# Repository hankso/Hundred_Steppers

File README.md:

## Hundred Steppers
An arduino library to control hundreds of steppers with as less pins or
arduinos as possible.

[74HC595](https://www.arduino.cc/en/Tutorial/ShiftOut) is needed to extend the
GPIO number of arduino.

To offer enough current for steppers, you may need UNL2803(8 channel NPN
darlington triodes, 500mA@50V max)

If you have used arduino library
[`Stepper`](https://www.arduino.cc/en/Reference/Stepper) and
[`Adafruit_NeoPixel`](https://github.com/adafruit/Adafruit_NeoPixel) before,
you may find this API familiar because I name these functions similar with them.

## How to use
- Download zip file
- Unzip in your arduino libraries directory. It can be `~/arduino/libraries`
or something like `C:\Program Files\Arduino\libraries`.
- open your arduino IDE and try include library `include <Hundred_Steppers.h>`,
also there is an [example](example/control_steppers) available.

## Hardware
- There is an example hardware design available in `Eagle` format.
- 74HC595 pins
    - ST_CP --> latchPin
    - SH_CP --> clockPin
    - DS --> dataPin
    - OE --> enablePin
    - MR --> clearPin

## API

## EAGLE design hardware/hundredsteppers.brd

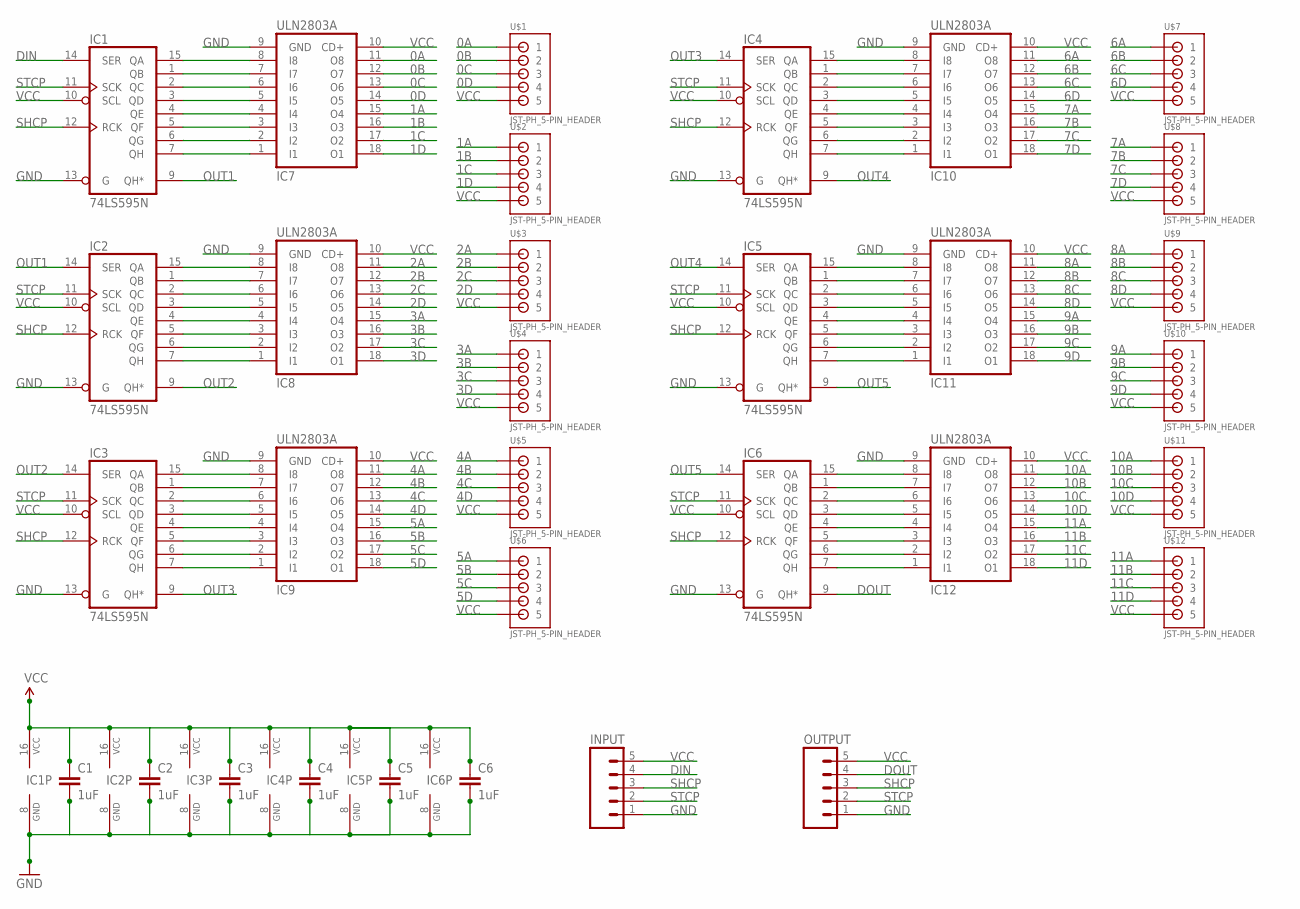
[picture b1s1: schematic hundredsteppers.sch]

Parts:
C1, C2, C3, C4, C5, C6: 1uF; 0805
IC1, IC2, IC3, IC4, IC5, IC6: 74LS595N; DIL16
IC7, IC8, IC9, IC10, IC11, IC12: ULN2803A; DIL18
INPUT: M05PTH; 1X05
OUTPUT: M05PTH; 1X05
U$1, U$2, U$3, U$4, U$5, U$6, U$7, U$8, U$9, U$10, U$11, U$12: JST-PH_5-PIN_HEADER; JST_B5B-PH_HEADER

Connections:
0A: IC7.11 (O8), U$1.P1 (1)
0B: IC7.12 (O7), U$1.P2 (2)
0C: IC7.13 (O6), U$1.P3 (3)
0D: IC7.14 (O5), U$1.P4 (4)
1A: IC7.15 (O4), U$2.P1 (1)
1B: IC7.16 (O3), U$2.P2 (2)
1C: IC7.17 (O2), U$2.P3 (3)
1D: IC7.18 (O1), U$2.P4 (4)
2A: IC8.11 (O8), U$3.P1 (1)
2B: IC8.12 (O7), U$3.P2 (2)
2C: IC8.13 (O6), U$3.P3 (3)
2D: IC8.14 (O5), U$3.P4 (4)
3A: IC8.15 (O4), U$4.P1 (1)
3B: IC8.16 (O3), U$4.P2 (2)
3C: IC8.17 (O2), U$4.P3 (3)
3D: IC8.18 (O1), U$4.P4 (4)
4A: IC9.11 (O8), U$5.P1 (1)
4B: IC9.12 (O7), U$5.P2 (2)
4C: IC9.13 (O6), U$5.P3 (3)
4D: IC9.14 (O5), U$5.P4 (4)
5A: IC9.15 (O4), U$6.P1 (1)
5B: IC9.16 (O3), U$6.P2 (2)
5C: IC9.17 (O2), U$6.P3 (3)
5D: IC9.18 (O1), U$6.P4 (4)
6A: IC10.11 (O8), U$7.P1 (1)
6B: IC10.12 (O7), U$7.P2 (2)
6C: IC10.13 (O6), U$7.P3 (3)
6D: IC10.14 (O5), U$7.P4 (4)
7A: IC10.15 (O4), U$8.P1 (1)
7B: IC10.16 (O3), U$8.P2 (2)
7C: IC10.17 (O2), U$8.P3 (3)
7D: IC10.18 (O1), U$8.P4 (4)
8A: IC11.11 (O8), U$9.P1 (1)
8B: IC11.12 (O7), U$9.P2 (2)
8C: IC11.13 (O6), U$9.P3 (3)
8D: IC11.14 (O5), U$9.P4 (4)
9A: IC11.15 (O4), U$10.P1 (1)
9B: IC11.16 (O3), U$10.P2 (2)
9C: IC11.17 (O2), U$10.P3 (3)
9D: IC11.18 (O1), U$10.P4 (4)
10A: IC12.11 (O8), U$11.P1 (1)
10B: IC12.12 (O7), U$11.P2 (2)
10C: IC12.13 (O6), U$11.P3 (3)
10D: IC12.14 (O5), U$11.P4 (4)
11A: IC12.15 (O4), U$12.P1 (1)
11B: IC12.16 (O3), U$12.P2 (2)
11C: IC12.17 (O2), U$12.P3 (3)
11D: IC12.18 (O1), U$12.P4 (4)
DIN: IC1.14 (SER), INPUT.4
DOUT: IC6.9 (QH*), OUTPUT.4
GND: C1.2, C2.2, C3.2, C4.2, C5.2, C6.2, IC1.8 (GND), IC1.13 (G), IC2.8 (GND), IC2.13 (G), IC3.8 (GND), IC3.13 (G), IC4.8 (GND), IC4.13 (G), IC5.8 (GND), IC5.13 (G), IC6.8 (GND), IC6.13 (G), IC7.9 (GND), IC8.9 (GND), IC9.9 (GND), IC10.9 (GND), IC11.9 (GND), IC12.9 (GND), INPUT.1, OUTPUT.1
unnamed: IC1.15 (QA), IC7.8 (I8)
unnamed: IC1.1 (QB), IC7.7 (I7)
unnamed: IC1.2 (QC), IC7.6 (I6)
unnamed: IC1.3 (QD), IC7.5 (I5)
unnamed: IC1.4 (QE), IC7.4 (I4)
unnamed: IC1.5 (QF), IC7.3 (I3)
unnamed: IC1.6 (QG), IC7.2 (I2)
unnamed: IC1.7 (QH), IC7.1 (I1)
unnamed: IC2.15 (QA), IC8.8 (I8)
unnamed: IC2.1 (QB), IC8.7 (I7)
unnamed: IC2.2 (QC), IC8.6 (I6)
unnamed: IC2.3 (QD), IC8.5 (I5)
unnamed: IC2.4 (QE), IC8.4 (I4)
unnamed: IC2.5 (QF), IC8.3 (I3)
unnamed: IC2.6 (QG), IC8.2 (I2)
unnamed: IC2.7 (QH), IC8.1 (I1)
unnamed: IC3.15 (QA), IC9.8 (I8)
unnamed: IC3.1 (QB), IC9.7 (I7)
unnamed: IC3.2 (QC), IC9.6 (I6)
unnamed: IC3.3 (QD), IC9.5 (I5)
unnamed: IC3.4 (QE), IC9.4 (I4)
unnamed: IC3.5 (QF), IC9.3 (I3)
unnamed: IC3.6 (QG), IC9.2 (I2)
unnamed: IC3.7 (QH), IC9.1 (I1)
unnamed: IC4.15 (QA), IC10.8 (I8)
unnamed: IC4.1 (QB), IC10.7 (I7)
unnamed: IC4.2 (QC), IC10.6 (I6)
unnamed: IC4.3 (QD), IC10.5 (I5)
unnamed: IC4.4 (QE), IC10.4 (I4)
unnamed: IC4.5 (QF), IC10.3 (I3)
unnamed: IC4.6 (QG), IC10.2 (I2)
unnamed: IC4.7 (QH), IC10.1 (I1)
unnamed: IC5.15 (QA), IC11.8 (I8)
unnamed: IC5.1 (QB), IC11.7 (I7)
unnamed: IC5.2 (QC), IC11.6 (I6)
unnamed: IC5.3 (QD), IC11.5 (I5)
unnamed: IC5.4 (QE), IC11.4 (I4)
unnamed: IC5.5 (QF), IC11.3 (I3)
unnamed: IC5.6 (QG), IC11.2 (I2)
unnamed: IC5.7 (QH), IC11.1 (I1)
unnamed: IC6.15 (QA), IC12.8 (I8)
unnamed: IC6.1 (QB), IC12.7 (I7)
unnamed: IC6.2 (QC), IC12.6 (I6)
unnamed: IC6.3 (QD), IC12.5 (I5)
unnamed: IC6.4 (QE), IC12.4 (I4)
unnamed: IC6.5 (QF), IC12.3 (I3)
unnamed: IC6.6 (QG), IC12.2 (I2)
unnamed: IC6.7 (QH), IC12.1 (I1)
OUT1: IC1.9 (QH*), IC2.14 (SER)
OUT2: IC2.9 (QH*), IC3.14 (SER)
OUT3: IC3.9 (QH*), IC4.14 (SER)
OUT4: IC4.9 (QH*), IC5.14 (SER)
OUT5: IC5.9 (QH*), IC6.14 (SER)
SHCP: IC1.12 (RCK), IC2.12 (RCK), IC3.12 (RCK), IC4.12 (RCK), IC5.12 (RCK), IC6.12 (RCK), INPUT.3, OUTPUT.3
STCP: IC1.11 (SCK), IC2.11 (SCK), IC3.11 (SCK), IC4.11 (SCK), IC5.11 (SCK), IC6.11 (SCK), INPUT.2, OUTPUT.2
VCC: C1.1, C2.1, C3.1, C4.1, C5.1, C6.1, IC1.10 (SCL), IC1.16 (VCC), IC2.10 (SCL), IC2.16 (VCC), IC3.10 (SCL), IC3.16 (VCC), IC4.10 (SCL), IC4.16 (VCC), IC5.10 (SCL), IC5.16 (VCC), IC6.10 (SCL), IC6.16 (VCC), IC7.10 (CD+), IC8.10 (CD+), IC9.10 (CD+), IC10.10 (CD+), IC11.10 (CD+), IC12.10 (CD+), INPUT.5, OUTPUT.5, U$1.P5 (5), U$2.P5 (5), U$3.P5 (5), U$4.P5 (5), U$5.P5 (5), U$6.P5 (5), U$7.P5 (5), U$8.P5 (5), U$9.P5 (5), U$10.P5 (5), U$11.P5 (5), U$12.P5 (5)

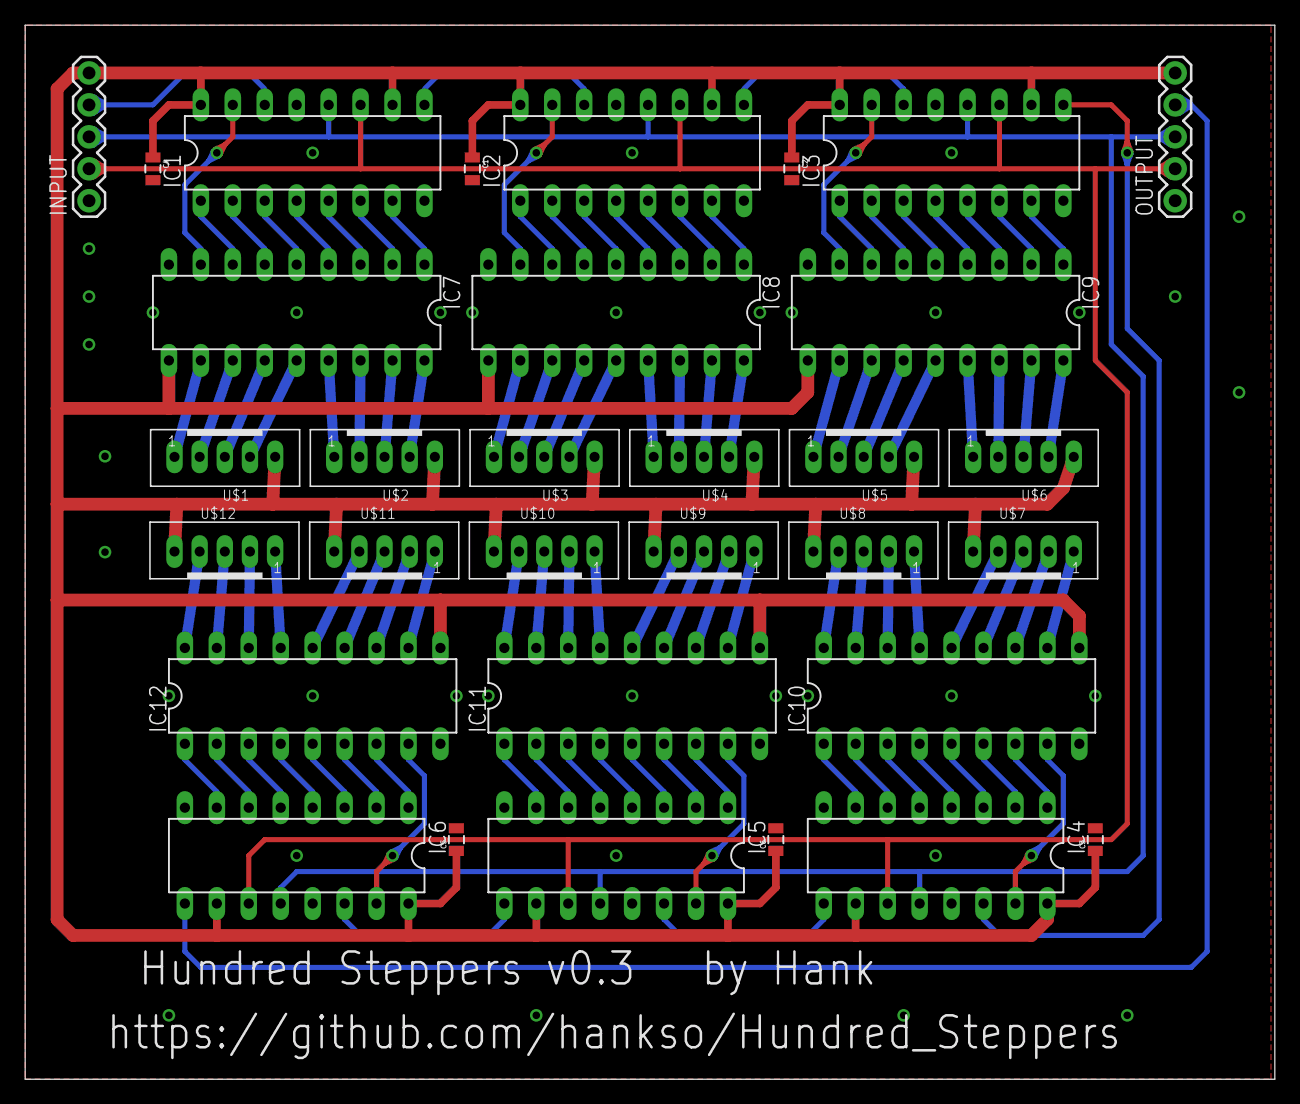
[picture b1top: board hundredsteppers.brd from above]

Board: 2 copper layers, 99.4 x 83.8 mm, 32 parts (0 on the bottom side), 107 nets.

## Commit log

2018-03-25 first push
2018-04-13 fix error on PCB
2018-05-25 only support 5-wires 4-phase stepper
2018-06-02 bugfix: STCP and SHCP changed
2018-07-17 Use correct field separator in keywords.txt
    The Arduino IDE requires the use of a single true tab separator between the keyword name and identifier. When spaces are used rather than a true tab the keyword is not highlighted.
    Reference:
    https://github.com/arduino/Arduino/wiki/Arduino-IDE-1.5:-Library-specification#keywords
2019-01-14 rename variables
2021-02-09 fix typo

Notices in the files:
parts and their libraries:
SparkFun-Connectors: Licensing: CC v3.0 Share-Alike You are welcome to use this library for commercial purposes.
